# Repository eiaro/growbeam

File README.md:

# GrowBeam

> A high-efficiency, open-source grow light module for indoor gardeners and hardware hackers.

**GrowBeam** is a modular open-source grow light system designed for indoor gardens, hydroponic setups, and controlled environment agriculture. Each module combines high-efficiency white and deep red LEDs to provide a balanced light spectrum optimized for plant growth.

**NOTE** A test batch is currently ordered. Details to follow soon(tm).

---

## 🌱 Features

- Modular and scalable design
- Uses Samsung LM301H (white) and LUXEON SunPlus 2835 (660 nm red) LEDs
- Designed for 42 V DC input (constant current)
- Simple current-limiting resistor configuration
- Passive cooling (no fans required)
- Easy to manufacture and assemble

## 💡 Light Output & Efficiency

GrowBeam is designed to deliver high photosynthetically active radiation (PAR) while consuming minimal power. Below is a breakdown of light performance based on actual component data:

These values are based on typical LED performance from manufacturer datasheets under standard current levels.

### 🔢 Estimated Output (Per Module)

| Component                   | Qty | PPF per LED (μmol/s) | Total PPF (μmol/s) |
|----------------------------|-----|-----------------------|---------------------|
| Samsung LM301H (white)     | 72  | ~0.56                 | ~40               |
| LUXEON 2835 Deep Red (660 nm) | 15  | ~0.60                 | ~9                |
| **Total**                  | –   | –                     | **~49 μmol/s**    |

- **Power consumption:** ~19 W  
- **Photosynthetic Photon Efficacy (PPE):** ~2.60 μmol/J

---

### 🔁 Comparison with Other Light Sources

| Light Source               | Power | PPF (μmol/s) | PPE (μmol/J) | Notes                           |
|---------------------------|--------|--------------|--------------|----------------------------------|
| **GrowBeam**              | ~19 W | ~49        | ~2.6        | High-efficiency DIY module ✅     |
| HPS 400W                  | 400 W  | ~550         | ~1.4         | High heat, low efficiency ❌      |
| Generic LED Panel (20W)   | 20 W   | ~15–20       | ~0.75–1.0    | Often misleading specs ❌        |
| T5 Fluorescent Tube (24W) | 24 W   | ~28          | ~1.2         | Narrow spectrum, low efficacy ❌ |
| Commercial Grow LED (LM301H) | 100 W | ~270         | ~2.7         | Comparable to GrowBeam ✅        |

---

GrowBeam matches the efficiency of premium grow lights using open hardware and off-the-shelf components — making it a great choice for small to medium-scale indoor growers.

---

## 🛠️ Hardware Overview

Each GrowBeam module contains:
- 6 LED strings with 12 × Samsung LM301H (white)
- 1 LED string with 15 × LUXEON SunPlus 2835 Deep Red

All strings are powered by a shared 42 V DC constant current source and operate at approx. 65 mA per string.

## 📋 Bill of Materials (BoM)

You’ll find a complete part list in `hardware/bom.csv`.  
Key components include:

- 72 × Samsung LM301H white LEDs
- 15 × LUXEON SunPlus 2835 Deep Red LEDs
- Al MCPCB (196 × 35 mm, aluminum-backed recommended)

---

## 📂 Repository Structure
```
growbeam/
├── hardware/
│   ├── kicad_project/           # Contains .kicad_pro, .kicad_sch, .kicad_pcb files, etc.
│   ├── exports/                 # Gerber files, BOM, pick & place, and fabrication outputs
│   └── bom.csv                  # Human-readable bill of materials (optional auto-generated)
├── docs/                        # Additional documentation, test results, diagrams
├── images/                      # Renders, module photos, screenshots
├── LICENSE                      # CERN-OHL v2-S license file
├── README.md                    # Project description and usage guide
├── .gitignore                   # Ignore KiCad backups and build artifacts
└── CONTRIBUTING.md              # (Optional) Contribution guidelines
```

---

## 🧪 Getting Started

1. Clone the repository:  
   `git clone https://github.com/eiaro/growbeam.git`
2. Open the KiCad project in `hardware/kicad_project/`
3. Order parts using the BOM (`hardware/bom.csv`)
4. Assemble and test each module with a 24 V power supply

---

## 📸 Gallery

*(Add photos or renders here)*  

---

## 📄 License

This project is licensed under the **CERN Open Hardware License v2-S (Strongly Reciprocal)**.  
See the [LICENSE](./LICENSE) file for full terms.

You are free to use, modify, manufacture, and distribute this project, provided that all modifications remain open under the same license.

---

## 🤝 Contributing

Contributions, improvements, and bug reports are welcome!  
If you build your own GrowBeam modules, feel free to share them via issues or pull requests.

## 🙏 Acknowledgements

- Samsung and Lumileds for their detailed datasheets and high-quality horticulture LEDs.
- Open Source Hardware community for inspiration and resources.

## 🌐 Community & Contact

Questions, ideas, or want to showcase your build?  
Open an [issue](https://github.com/eiaro/growbeam/issues) or reach out via [@eiaro](https://github.com/eiaro).

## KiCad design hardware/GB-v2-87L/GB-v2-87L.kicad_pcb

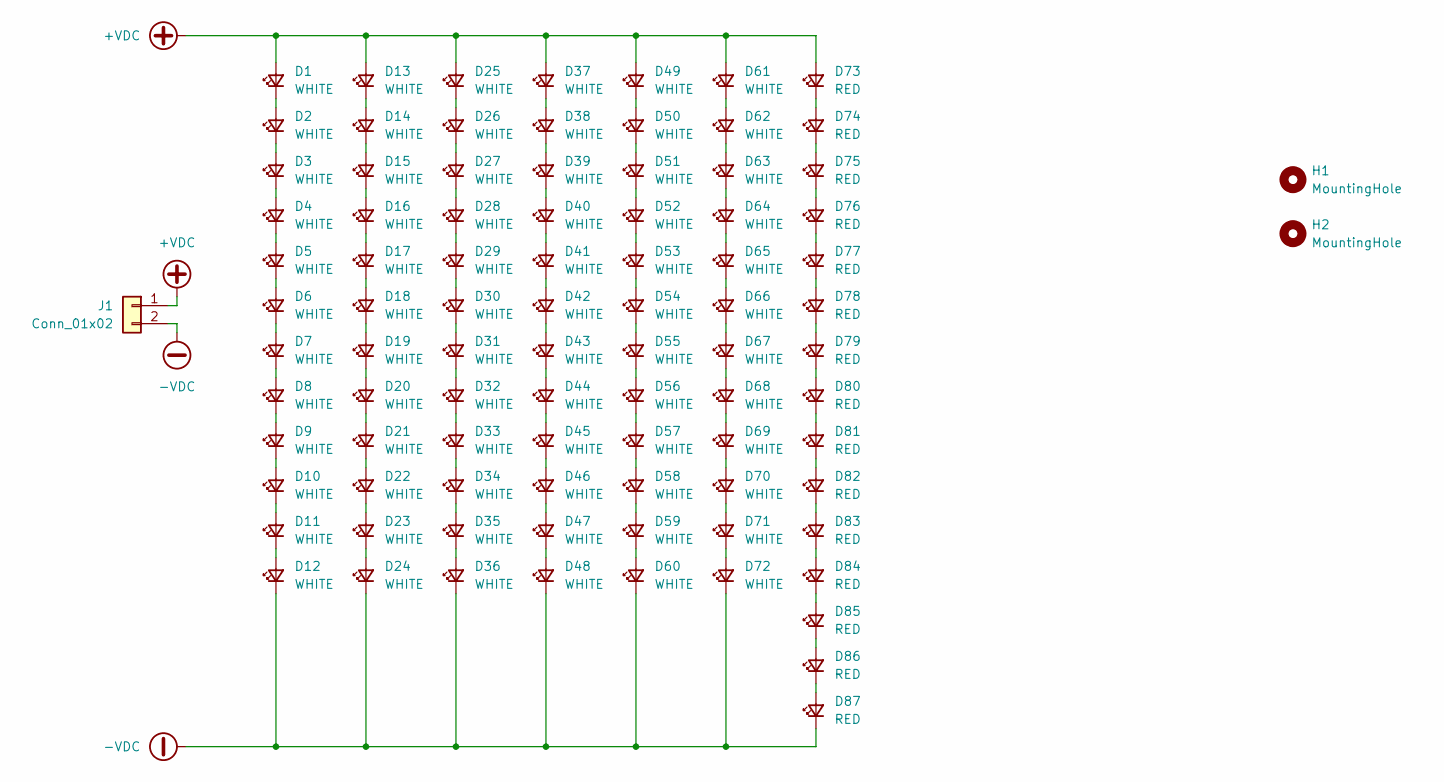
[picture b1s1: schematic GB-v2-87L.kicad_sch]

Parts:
D1, D2, D3, D4, D5, D6, D7, D8, D9, D10, D11, D12, D13, D14, D15, D16, D17, D18, D19, D20, D21, D22, D23, D24, D25, D26, D27, D28, D29, D30, D31, D32, D33, D34, D35, D36, D37, D38, D39, D40, D41, D42, D43, D44, D45, D46, D47, D48, D49, D50, D51, D52, D53, D54, D55, D56, D57, D58, D59, D60, D61, D62, D63, D64, D65, D66, D67, D68, D69, D70, D71, D72: WHITE; LED_LM301H_1212
D73, D74, D75, D76, D77, D78, D79, D80, D81, D82, D83, D84, D85, D86, D87: RED; LED-SP2835-LUMILEDS
H1, H2: MountingHole; MountingHole_2.7mm
J1: Conn_01x02; WAGO_2060-452_998-404

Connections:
+VDC: D1.2 (A), D13.2 (A), D25.2 (A), D37.2 (A), D49.2 (A), D61.2 (A), D73.2 (A), J1.1
-VDC: D12.1 (K), D24.1 (K), D36.1 (K), D48.1 (K), D60.1 (K), D72.1 (K), D87.1 (K), J1.2
unnamed: D1.1 (K), D2.2 (A)
unnamed: D2.1 (K), D3.2 (A)
unnamed: D3.1 (K), D4.2 (A)
unnamed: D4.1 (K), D5.2 (A)
unnamed: D5.1 (K), D6.2 (A)
unnamed: D6.1 (K), D7.2 (A)
unnamed: D7.1 (K), D8.2 (A)
unnamed: D8.1 (K), D9.2 (A)
unnamed: D9.1 (K), D10.2 (A)
unnamed: D10.1 (K), D11.2 (A)
unnamed: D11.1 (K), D12.2 (A)
unnamed: D13.1 (K), D14.2 (A)
unnamed: D14.1 (K), D15.2 (A)
unnamed: D15.1 (K), D16.2 (A)
unnamed: D16.1 (K), D17.2 (A)
unnamed: D17.1 (K), D18.2 (A)
unnamed: D18.1 (K), D19.2 (A)
unnamed: D19.1 (K), D20.2 (A)
unnamed: D20.1 (K), D21.2 (A)
unnamed: D21.1 (K), D22.2 (A)
unnamed: D22.1 (K), D23.2 (A)
unnamed: D23.1 (K), D24.2 (A)
unnamed: D25.1 (K), D26.2 (A)
unnamed: D26.1 (K), D27.2 (A)
unnamed: D27.1 (K), D28.2 (A)
unnamed: D28.1 (K), D29.2 (A)
unnamed: D29.1 (K), D30.2 (A)
unnamed: D30.1 (K), D31.2 (A)
unnamed: D31.1 (K), D32.2 (A)
unnamed: D32.1 (K), D33.2 (A)
unnamed: D33.1 (K), D34.2 (A)
unnamed: D34.1 (K), D35.2 (A)
unnamed: D35.1 (K), D36.2 (A)
unnamed: D37.1 (K), D38.2 (A)
unnamed: D38.1 (K), D39.2 (A)
unnamed: D39.1 (K), D40.2 (A)
unnamed: D40.1 (K), D41.2 (A)
unnamed: D41.1 (K), D42.2 (A)
unnamed: D42.1 (K), D43.2 (A)
unnamed: D43.1 (K), D44.2 (A)
unnamed: D44.1 (K), D45.2 (A)
unnamed: D45.1 (K), D46.2 (A)
unnamed: D46.1 (K), D47.2 (A)
unnamed: D47.1 (K), D48.2 (A)
unnamed: D49.1 (K), D50.2 (A)
unnamed: D50.1 (K), D51.2 (A)
unnamed: D51.1 (K), D52.2 (A)
unnamed: D52.1 (K), D53.2 (A)
unnamed: D53.1 (K), D54.2 (A)
unnamed: D54.1 (K), D55.2 (A)
unnamed: D55.1 (K), D56.2 (A)
unnamed: D56.1 (K), D57.2 (A)
unnamed: D57.1 (K), D58.2 (A)
unnamed: D58.1 (K), D59.2 (A)
unnamed: D59.1 (K), D60.2 (A)
unnamed: D61.1 (K), D62.2 (A)
unnamed: D62.1 (K), D63.2 (A)
unnamed: D63.1 (K), D64.2 (A)
unnamed: D64.1 (K), D65.2 (A)
unnamed: D65.1 (K), D66.2 (A)
unnamed: D66.1 (K), D67.2 (A)
unnamed: D67.1 (K), D68.2 (A)
unnamed: D68.1 (K), D69.2 (A)
unnamed: D69.1 (K), D70.2 (A)
unnamed: D70.1 (K), D71.2 (A)
unnamed: D71.1 (K), D72.2 (A)
unnamed: D73.1 (K), D74.2 (A)
unnamed: D74.1 (K), D75.2 (A)
unnamed: D75.1 (K), D76.2 (A)
unnamed: D76.1 (K), D77.2 (A)
unnamed: D77.1 (K), D78.2 (A)
unnamed: D78.1 (K), D79.2 (A)
unnamed: D79.1 (K), D80.2 (A)
unnamed: D80.1 (K), D81.2 (A)
unnamed: D81.1 (K), D82.2 (A)
unnamed: D82.1 (K), D83.2 (A)
unnamed: D83.1 (K), D84.2 (A)
unnamed: D84.1 (K), D85.2 (A)
unnamed: D85.1 (K), D86.2 (A)
unnamed: D86.1 (K), D87.2 (A)

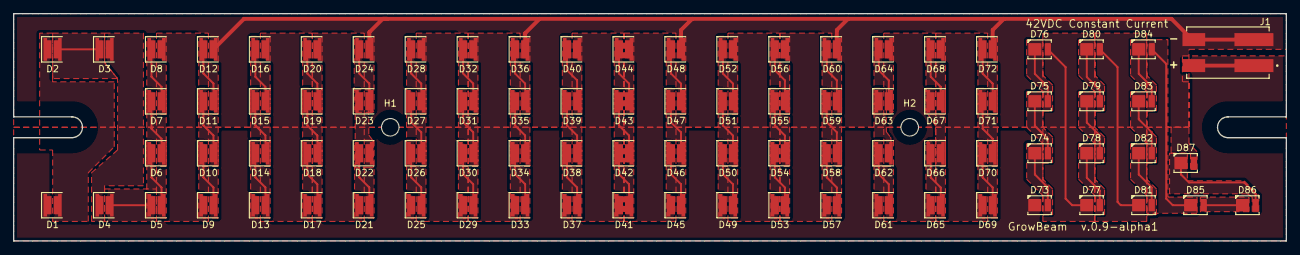
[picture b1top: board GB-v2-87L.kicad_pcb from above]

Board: 2 copper layers, 196.0 x 35.0 mm, 90 parts (0 on the bottom side), 82 nets.

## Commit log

2025-04-17 Create LICENSE
2025-04-17 Changed footprint for L1SP. Added color 3D models. Rerouted after changed footprints.
2025-04-17 Changes to README
2025-04-17 Adding stuff to setup CI
2025-04-17 First try of getting this done automatic
2025-04-17 Added pull_request
2025-04-17 Misplaced file
2025-04-17 Update Dockerfile
2025-04-18 Edits to gitignore file
2025-04-18 renaming files for my ocd
2025-04-18 my ocd
2025-04-18 Remove unused KiCad project file for growlight module
2025-04-18 Update commit-exports.yml
    Using full paths for export and adding debug help
2025-04-18 Update commit-exports.yml
    Using artifacts to transfer files
2025-04-18 Update commit-exports.yml
    bom.csv should be generated and not uploaded, so we keep the .gitignore and add a -f flag.
2025-04-18 Update commit-exports.yml
    Giving write access
2025-04-18 Rename kicad9-ci.yml to kicad9-ci.yml.inactive
2025-04-18 Rename commit-exports.yml to commit-exports.yml.inactive
2025-04-18 Test export CI
2025-04-18 Remove dummy test files from kicad_project
2025-04-18 Update export workflow to include permissions and auto-generate files after checks
2025-04-18 Add dummy file to kicad_project for placeholder purposes
2025-04-18 Update dummy file in kicad_project to specify version
2025-04-18 Refactor export workflow to commit generated files directly instead of creating a pull request
2025-04-18 Update dummy file in kicad_project to change content
2025-04-18 Auto-generate files after ERC/DRC checks
2025-04-18 Add google site verification file
2025-04-18 Add Hugo site deployment workflow and initial documentation files
2025-04-18 Update Hugo action version in deployment workflow
2025-04-18 Update workflow name for clarity in Hugo site deployment
2025-04-18 Fix workflow name punctuation in GitHub Pages deployment
2025-04-18 Add Ananke theme as submodule
2025-04-18 Add SEO metadata and robots.txt for improved search engine indexing
2025-04-19 Update issue templates
2025-04-19 Fix Dockerfile to specify full image path for KiCad
2025-04-19 Update .gitignore and CONTRIBUTING.md; add Makefile for containerized testing
2025-04-19 Add FreeCAD and Blender steps for STEP to STL conversion and rendering
2025-04-19 Fix KiCad commands in export workflow for ERC and DRC checks
2025-04-19 Add missing exports for growbeam.stl and growbeam.png in workflow
2025-04-21 Add GitHub Actions workflow for building and pushing Docker image to GHCR
2025-04-21 Refactor Dockerfile to use Ubuntu base image and streamline installation of dependencies for KiCad, Blender, and FreeCAD
2025-04-21 Refactor export workflow: streamline steps and enhance rendering process
2025-04-21 Remove deprecated rendering scripts for STEP to STL and PNG conversion
2025-04-21 Fix Dockerfile path in build-image target of Makefile
2025-04-21 Add severity flag to ERC and DRC checks in Makefile
2025-04-21 Add severity flag to ERC and DRC checks in GitHub Actions workflow
2025-04-21 Update ERC exclusions and correct filename in KiCad project
2025-04-21 Update export workflow to trigger on successful ERC and DRC completion
2025-04-21 Fix via position in KiCad PCB layout
2025-04-21 Remove unused dummy file from KiCad project
2025-04-21 Update .gitignore to exclude all files in the hardware/exports/ directory
2025-04-21 Add rectangular outline to LED footprint for improved visibility
2025-04-21 Implement new pcb land and a few adjustments
2025-04-22 Update git ignore
2025-04-22 Updated structure
2025-04-22 Theme
2025-04-22 removed submodule
2025-04-22 index
2025-04-22 Moving reference docs
2025-04-22 Refactor documentation structure: remove outdated files, add new sections on background, components, design, and getting started
2025-04-23 Add Inkscape installation to Dockerfile
2025-04-23 Update Dockerfile
    Added inkscape
2025-04-23 Refactor export process in GitHub Actions and Makefile: streamline KiCad file exports and update image reference
2025-04-23 Fix image reference in schematic documentation: update Schematic image path to relative URL
2025-04-23 Add SVG optimization script: implement functions to remove white backgrounds and crop SVGs using Inkscape
2025-04-23 Refactor documentation and add BOM generation script
    - Removed the Table of Contents from components index.
    - Updated the schematic documentation to reference the BOM markdown file.
    - Corrected the link for Background & Motivation in the main index.
    - Added MathJax configuration for rendering mathematical expressions.
    - Included extra JavaScript file for MathJax in mkdocs configuration.
    - Created a new Python script to generate BOM in markdown format from CSV.
2025-04-23 Update .gitignore, Makefile, Dockerfile, and documentation: add virtual environment, streamline export processes, and include BOM in documentation
2025-04-23 Enhance BOM configuration: add presets for BOM export with detailed field settings and grouping options
2025-04-23 Add deployment workflow for documentation to GitHub Pages
2025-04-23 fix Makefile
2025-04-23 Fix BOM Markdown generation by ensuring the output directory exists
2025-04-23 Fix typo in Makefile: change 'makedir' to 'mkdir' for BOM Markdown generation
2025-04-23 deploy: 6a2e26ba41b080a5225e482da8e48eb6865ad810
2025-04-23 Add site_url to mkdocs.yml for proper site linking
2025-04-23 deploy: 54dba07bb04c56e6c82dae0fe7c1e4895c02d57e
2025-04-23 Add GitHub Actions workflow for production release and update Makefile for production preparation
2025-04-23 deploy: 224bb205258406eabdb6747b105e895e5e66b2d9
2025-04-24 Enhance Dockerfile and entrypoint script: add wxpython-tools, additional Python packages, and create entrypoint.sh for virtual environment activation
2025-04-24 deploy: ebbdd50fbbd949e433a8637bc002502d79114651
2025-04-24 Update GitHub Actions workflow and Makefile for production release: add build-image step, enhance export rules, and update README generation
2025-04-24 deploy: 59d19e8ee037c2b84f098f9ba745729f1c78b132
2025-05-02 Refactor code structure for improved readability and maintainability
2025-05-02 Add new footprints and symbols for various components
    - Created footprint for LED-SP2835-LUMILEDS with detailed properties and dimensions.
    - Added footprint for TE_2834167-3 terminal block with appropriate pads and silk screen.
    - Introduced WAGO_2060-452_998-404 and WAGO_2060-453_998-404 footprints with defined pads and outlines.
    - Updated fp-lib-table to include new libraries for LED and terminal blocks.
    - Added sym-lib-table for new symbols related to WAGO terminal blocks.
    - Created symbols for WAGO_2060-452_998-404 and WAGO_2060-453_998-404 with relevant properties and pin configurations.
2025-05-02 Update schematic and PCB paths in Makefile to reflect new project structure
2025-05-02 Refactor GitHub Actions and Makefile for ERC and DRC checks: streamline commands using Makefile targets and update output paths
2025-05-02 Fix typo in .gitignore: update 'fp_info-cache' to 'fp-info-cache'
2025-05-02 Add mechanical design and production documentation
    - Created mechanical design documentation outlining the frame specifications for module mounting.
    - Added production documentation detailing PCB specifications, assembly instructions, operation and safety guidelines, and future plans for enhancements.
    - Included a lock file for the schematic to track user access.
2025-05-02 Update GrowBeam documentation and hardware configuration
    - Changed the module configuration in the documentation from 5 × 5 to 2 × 5.
    - Removed extensive default settings and rules from the KiCad project file to streamline the configuration.
    - Adjusted track width from 0.3 to 0.2 in the KiCad project.
    - Updated BOM presets to include detailed fields for better organization and clarity.
    - Modified label size ratio and text offset ratio for improved readability in the schematic.
2025-05-02 deploy: 04ff3c4a44d576119790cf79b1c575f4a328643a
2025-05-03 - Introduced a new footprint for a 2.7mm mounting hole in the ProjectSpecific library. - Updated schematic references to use the new footprint instead of the previous generic mounting hole.
2025-05-03 deploy: 54dff5277fd3f0f88f9713288c6ab6d1a6ec607b
2025-05-04 Update README.md with revised specifications and test batch note
2025-05-04 deploy: f35e8399a7e034916b57fea92fbe41a7b9f37a80
2025-05-04 deploy: 063de9692e8284e90c97f92b71f57bdbb6d48820

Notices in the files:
README.md:
License: CERN-OHL-S
